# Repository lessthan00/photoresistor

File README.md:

# photoresistor

模块参考
https://item.taobao.com/item.htm?id=39878225784&spm=a21wu.12321156.0.0.6f06584cNpolGY

比较器 LM393  
https://www.jlc-smt.com/lcsc/detail?componentCode=C400839  
VIN 2V~36V  

可调电阻  RM065-103(10K)  
https://www.jlc-smt.com/lcsc/detail?componentCode=C5205021  

光敏电阻 GL5506（4-7K）  
https://www.jlc-smt.com/lcsc/detail?componentCode=C11299  
暗电阻500K,亮电阻4K,p=3mm

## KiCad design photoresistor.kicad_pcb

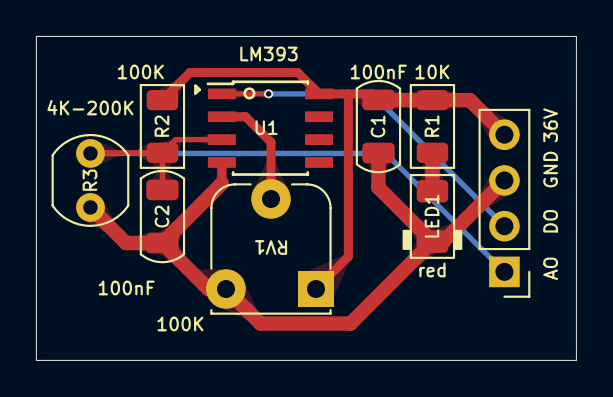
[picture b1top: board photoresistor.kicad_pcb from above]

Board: 2 copper layers, 30.0 x 18.0 mm, 9 parts (0 on the bottom side), 6 nets.

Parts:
C1, C2: 100nF; C_1206_3216Metric
J1: Conn_01x04; PinHeader_1x04_P2.54mm_Vertical
LED1: red; LED_1206_3216Metric
R1: 10K; R_1206_3216Metric
R2: 100K; R_1206_3216Metric
R3: 4K-200K; R_LDR_5.0x4.1mm_P3mm_Vertical
RV1: 100K; Potentiometer_RM065
U1: LM393; SOIC-8_3.9x4.9mm_Pitch1.27mm

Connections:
+36V: C1.1, J1.4, R1.1, R2.1, RV1.1, U1.8 (V+)
/AO: C2.1, J1.1, R2.2, R3.1, U1.3 (+)
/DO: J1.2, U1.1
GND: C1.2, C2.2, J1.3, LED1.1 (K), R3.2, RV1.3, U1.4 (V-)
unnamed: LED1.2 (A), R1.2
unnamed: RV1.2, U1.2 (-)
